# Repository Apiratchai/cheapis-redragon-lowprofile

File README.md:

```mermaid
graph TD;

subgraph In_Progress
  id1["Cherry MX, Kailh Choc V1"] --> id2["Redragon Low Profile (reversible)"] --> id3["All MX, Kailh Choc V1, Redragon low profile switches support (In Branch)"];

end

subgraph To_Do
  A["Laser cut switch-bottom plates (minimalist, full plate, etc)"];
  B["space bar bridged version"];
  C["mill max 0305 compatability test"];
  D["Encoders or more switches n the thumb cluster"]

end

```
- Kicad 9.0 or newer maybe required
- This project aims to change only the switch being used while minimizing changes to everything else to maintain the best compatibility.
- This is my first time using KiCad. May you and the Lord forgive me if files contain any mistakes or issues (It's the reason why I remove the support for both MX and Choc V1, I wasn't sure if I can make it work).
- [Redragon Low Profile footprint]( https://github.com/rgoulter/keyboard-labs/blob/master/pcb/ProjectLocal.pretty/SW_Redragon_LowProfile_PCB_1.00u.kicad_mod
) is from  [Rgoulter](https://github.com/rgoulter). Kudos to this man.

Original PCB

Redragon PCB

If I just put redragon footprint on top of the old design, I think this will work with minimal change to the number 2 pad (make it smaller ?) I will try, 2$ per order anyway.

First Protorype I ordered on JLCPCB. If you notice the wires not connected, it has been fixed (maybe).

# cheapis (The Original)

v0.1 issues:
- most ubs cables cannot be plugged in when the pro micro is soldered in an usual way (upright, with the usually included pins), because of the top middle buttons. It has to be solderes upside down, flush with the keyboard pcb.
- not really an issue, but SOD-323 diodes are challenging to solder. They're also not the cheapest, although the difference is minuscule.

Cheapis was inspired by ferris and sweep.

It is the cheapest alternative to the above keyboards (that still has a PCB) as it is sub 100x100mm in size so it can be ordered for a very low price and it only needs one controller (Pro Micro or alternative).

Specs:
- Split
- Unibody
- 34 key
- Compatible with MX, Kailh Choc v1 and Gateron low profile switches
- needs 1n4148 SOD-323 diodes
- 19mm standard spacing
- angled sides by 20 degree

Pros:
- less than 100x100mm
- reversible, so you can order less
- needs ony one Pro Micro or alternative
- very cheap way to experiment with 34 key layout

Cons:
- it has to be unibody
- tenting is not possible
- fragile without a plate as the Pro Micro keeps the two sides together
- not much features, it's hardly more than a hardwire

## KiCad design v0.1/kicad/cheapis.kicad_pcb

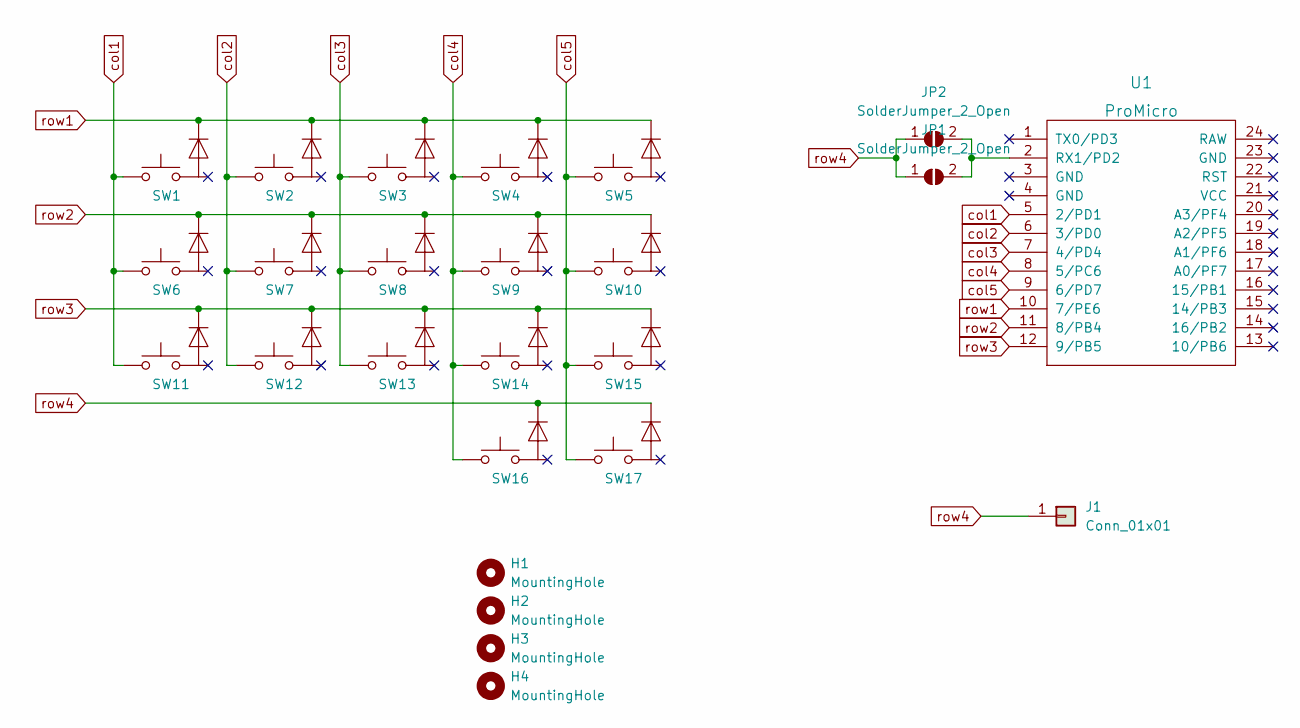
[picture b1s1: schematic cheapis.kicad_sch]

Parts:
H1, H2, H3, H4: MountingHole; MountingHole_2.2mm_M2_Pad_Via
J1: Conn_01x01; SolderWire-0.1sqmm_1x01_D0.4mm_OD1mm
JP1, JP2: SolderJumper_2_Open; SolderJumper-2_P1.3mm_Open_TrianglePad1.0x1.5mm
SW1, SW2, SW3, SW4, SW5, SW6, SW7, SW8, SW9, SW10, SW11, SW12, SW13, SW14, SW15, SW16, SW17: SW_Diode_Combined; MultiSwitches_MX_Redragon_ChocV1
U1: ProMicro; promicro_half

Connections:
unnamed: JP1.2 (B), JP2.2 (B), U1.2 (RX1/PD2)
col1: SW1.1, SW6.1, SW11.1, U1.5 (2/PD1)
col2: SW2.1, SW7.1, SW12.1, U1.6 (3/PD0)
col3: SW3.1, SW8.1, SW13.1, U1.7 (4/PD4)
col4: SW4.1, SW9.1, SW14.1, SW16.1, U1.8 (5/PC6)
col5: SW5.1, SW10.1, SW15.1, SW17.1, U1.9 (6/PD7)
row1: SW1.3, SW2.3, SW3.3, SW4.3, SW5.3, U1.10 (7/PE6)
row2: SW6.3, SW7.3, SW8.3, SW9.3, SW10.3, U1.11 (8/PB4)
row3: SW11.3, SW12.3, SW13.3, SW14.3, SW15.3, U1.12 (9/PB5)
row4: J1.1, JP1.1 (A), JP2.1 (A), SW16.3, SW17.3

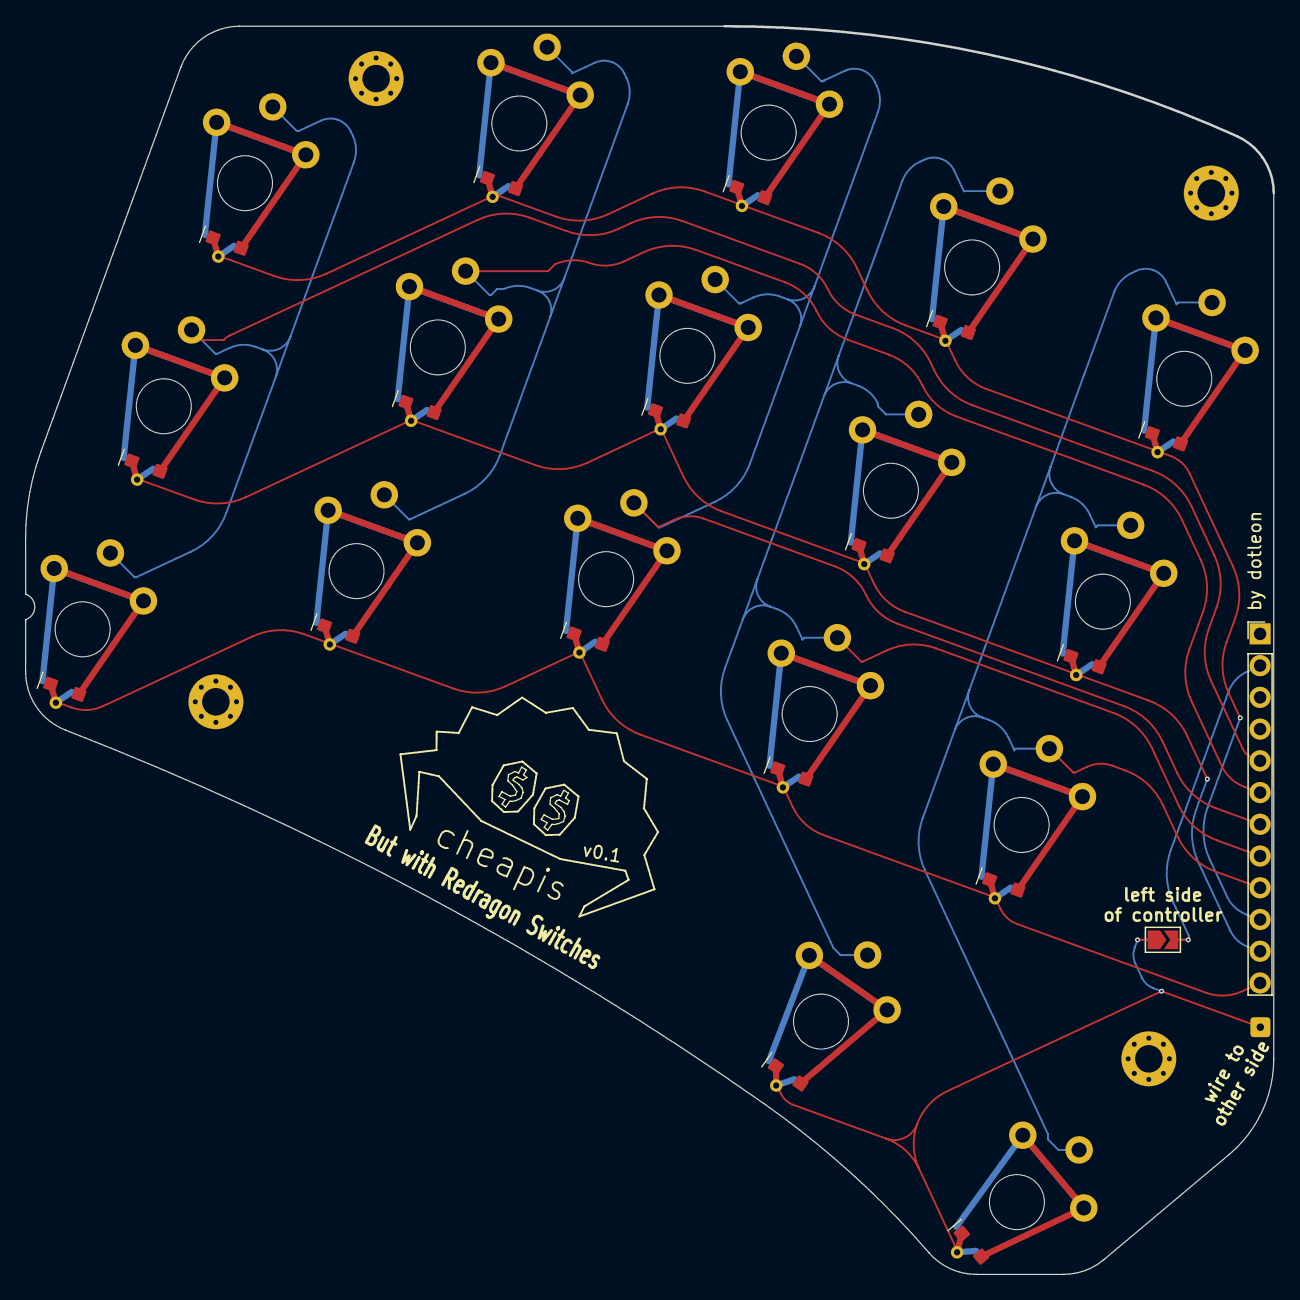
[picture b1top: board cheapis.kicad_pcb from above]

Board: 2 copper layers, 99.8 x 99.8 mm, 25 parts (1 on the bottom side), 10 nets.

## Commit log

2025-03-05 add customized SW_Redragon_LowProfile_1.00u footprint
2025-03-05 first prototype design
2025-03-05 Rename complete layers red dragon.png to complete layers redragon.png
2025-03-06 fix missing files
2025-03-06 multi-switches-support
2025-03-06 add footprint file, update readme
2025-03-10 add .gitignore
2025-03-10 fix some major design problem, rows not fully connected
2025-03-10 Rename cheapis.zip to GERBER.zip
